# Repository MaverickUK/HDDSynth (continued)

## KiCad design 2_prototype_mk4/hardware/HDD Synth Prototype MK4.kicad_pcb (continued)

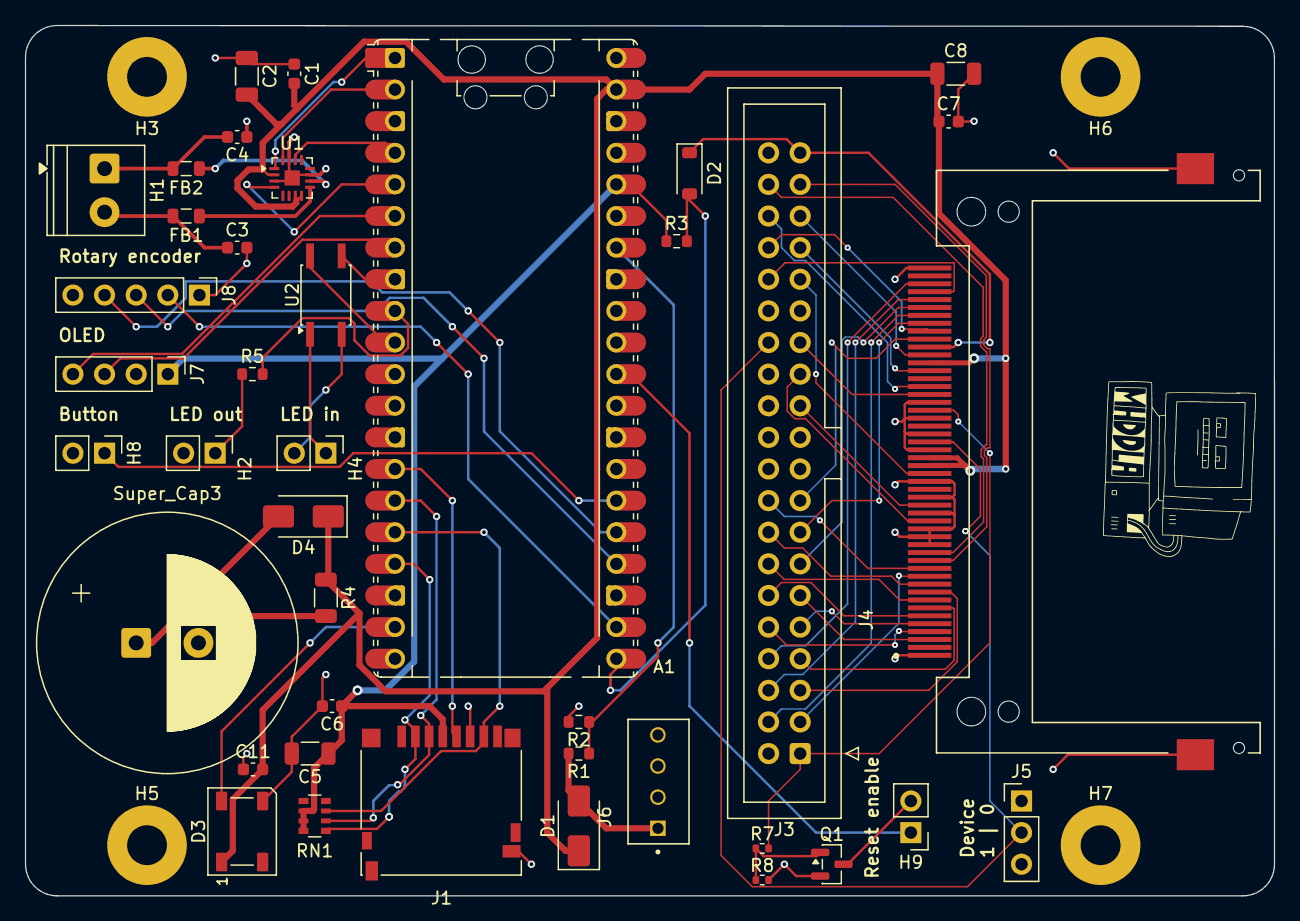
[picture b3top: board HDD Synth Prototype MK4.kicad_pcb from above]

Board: 2 copper layers, 100.3 x 69.9 mm, 44 parts (0 on the bottom side), 64 nets.

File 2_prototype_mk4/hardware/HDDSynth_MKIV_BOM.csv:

"Reference","Qty","Value","DNP","Exclude from BOM","Exclude from Board","Footprint","Datasheet","Description"
"A1","1","RaspberryPi_Pico2","","","","Module:RaspberryPi_Pico_Common_Unspecified","https://pip-assets.raspberrypi.com/categories/1005-raspberry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","High-performance microcontroller module featuring the RP2350 chip; dual-core ARM Cortex-M33 or Hazard3 RISC-V processors up to 150 MHz, 520kB SRAM, and 4MB off-chip QSPI flash"
"C1,C6,C7","3","0.1uF","","","","Capacitor_SMD:C_0603_1608Metric","","Unpolarized capacitor"
"C2,C5,C8","3","10uF","","","","Capacitor_SMD:C_1206_3216Metric","","Unpolarized capacitor"
"C3,C4","2","1nF","","","","Capacitor_SMD:C_0603_1608Metric","","Unpolarized capacitor, small symbol"
"C9,C10","2","100nF","","","","Capacitor_SMD:C_0402_1005Metric","","Unpolarized capacitor"
"D1","1","SS14","","","","Diode_SMD:D_SMA","","1A, 40V Schottky diode"
"D2","1","BAT43W","","","","Diode_SMD:D_SOD-123","","Schottky Barrier Diode, Low Forward Voltage (Vf ≈ 0.3V), 30V 200mA,"
"D4","1","SS12","","","","Diode_SMD:D_SMA","","Schottky diode"
"FB1,FB2","2","FerriteBead_Small","","","","Inductor_SMD:L_0805_2012Metric","","Ferrite bead, small symbol"
"H1","1","Conn_01x02","","","","TerminalBlock_Phoenix:TerminalBlock_Phoenix_PT-1,5-2-3.5-H_1x02_P3.50mm_Horizontal","","Generic connector, single row, 01x02, script generated (kicad-library-utils/schlib/autogen/connector/)"
"H2,H4,H8","3","Conn_01x02","","","","Connector_PinHeader_2.54mm:PinHeader_1x02_P2.54mm_Vertical","","Generic connector, single row, 01x02, script generated (kicad-library-utils/schlib/autogen/connector/)"
"J1","1","Micro_SD_Card","","","","Connector_Card:microSD_HC_Hirose_DM3D-SF","","Micro SD Card Socket - Hirose DM3D-SF"
"J3","1","Conn_02x20_Odd_Even","","","","Connector_IDC:IDC-Header_2x20_P2.54mm_Vertical","https://www.lcsc.com/product-detail/C19193815.html?s_z=n_q_p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","Generic connector, double row, 02x20, odd/even pin numbering scheme (row 1 odd numbers, row 2 even numbers), script generated (kicad-library-utils/schlib/autogen/connector/)"
"J4","1","1734451-1","","","","Custom:TE_1734451-1","https://www.snapeda.com/parts/1734451-1/TE%20Connectivity/vi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","50 Position Card Connector CompactFlash® - Type I, II Surface Mount, Right Angle Gold"
"J5","1","Conn_01x03_Pin","","","","Connector_PinHeader_2.54mm:PinHeader_1x03_P2.54mm_Vertical","","Generic connector, single row, 01x03, script generated"
"J6","1","171825-4","","","","Custom:TE_171825-4","","CONNECTOR, EIS, TYPE V, HEADER, 4 POSITION, 2.50 MM CENTERLINE | TE Connectivity 171825-4"
"J7","1","Conn_01x04_Pin","","","","Connector_PinHeader_2.54mm:PinHeader_1x04_P2.54mm_Vertical","","Generic connector, single row, 01x04, script generated"
"J8","1","Conn_01x05","","","","Connector_PinHeader_2.54mm:PinHeader_1x05_P2.54mm_Vertical","","Generic connector, single row, 01x05, script generated (kicad-library-utils/schlib/autogen/connector/)"
"R1","1","1K","","","","Resistor_SMD:R_0603_1608Metric","","Resistor"
"R2","1","2K","","","","Resistor_SMD:R_0603_1608Metric","","Resistor"
"R3","1","4.7K","","","","Resistor_SMD:R_0603_1608Metric","","Resistor"
"R4","1","33R","","","","Resistor_SMD:R_1206_3216Metric","","Resistor"
"R5","1","330R","","","","Resistor_SMD:R_0603_1608Metric","","Resistor"
"R6","1","10K","","","","Resistor_SMD:R_0402_1005Metric","","Resistor"
"RN1","1","47K","","","","Resistor_SMD:R_Array_Convex_4x0603","","4 resistor network, parallel topology"
"Super_Cap3","1","1F","","","","Capacitor_THT:CP_Radial_D14.0mm_P5.00mm","https://resources.kitronik.co.uk/pdf/super_capacitor.pdf","polarized radial super capacitor, 1F 5.5V"
"U1","1","MAX98357A","","","","Package_DFN_QFN:TQFN-16-1EP_3x3mm_P0.5mm_EP1.23x1.23mm","https://www.analog.com/media/en/technical-documentation/data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","Mono DAC with amplifier, I2S, PCM, TDM, 32-bit, 96khz, 3.2W, TQFP-16"
"U2","1","Optocoupler_DC_PhotoNPN_AKEC","","","","Package_SO:SO-4_4.4x3.6mm_P2.54mm","","Generic DC optocoupler with NPN phototransistor output, pins order: anode/cathode/emitter/collector"
"U3","1","TXS0101DBV","","","","Package_TO_SOT_SMD:SOT-23-6","https://www.ti.com/lit/ds/symlink/txs0101.pdf","1-Bit Bidirectional Voltage-Level Shifter for Open-Drain and Push-Pull Application, SOT-23"

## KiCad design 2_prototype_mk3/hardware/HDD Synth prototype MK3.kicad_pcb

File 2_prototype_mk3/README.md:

## HDD Synth
### Prototype MKIII

#### Hardware
Designed in KiCad and manufacufered by PCBWay with factory assembly of components

Uses mostly surface mounted components for ease of automated assembly and reduction in size and cost

#### Software
Runs CircuitPython for ease of development

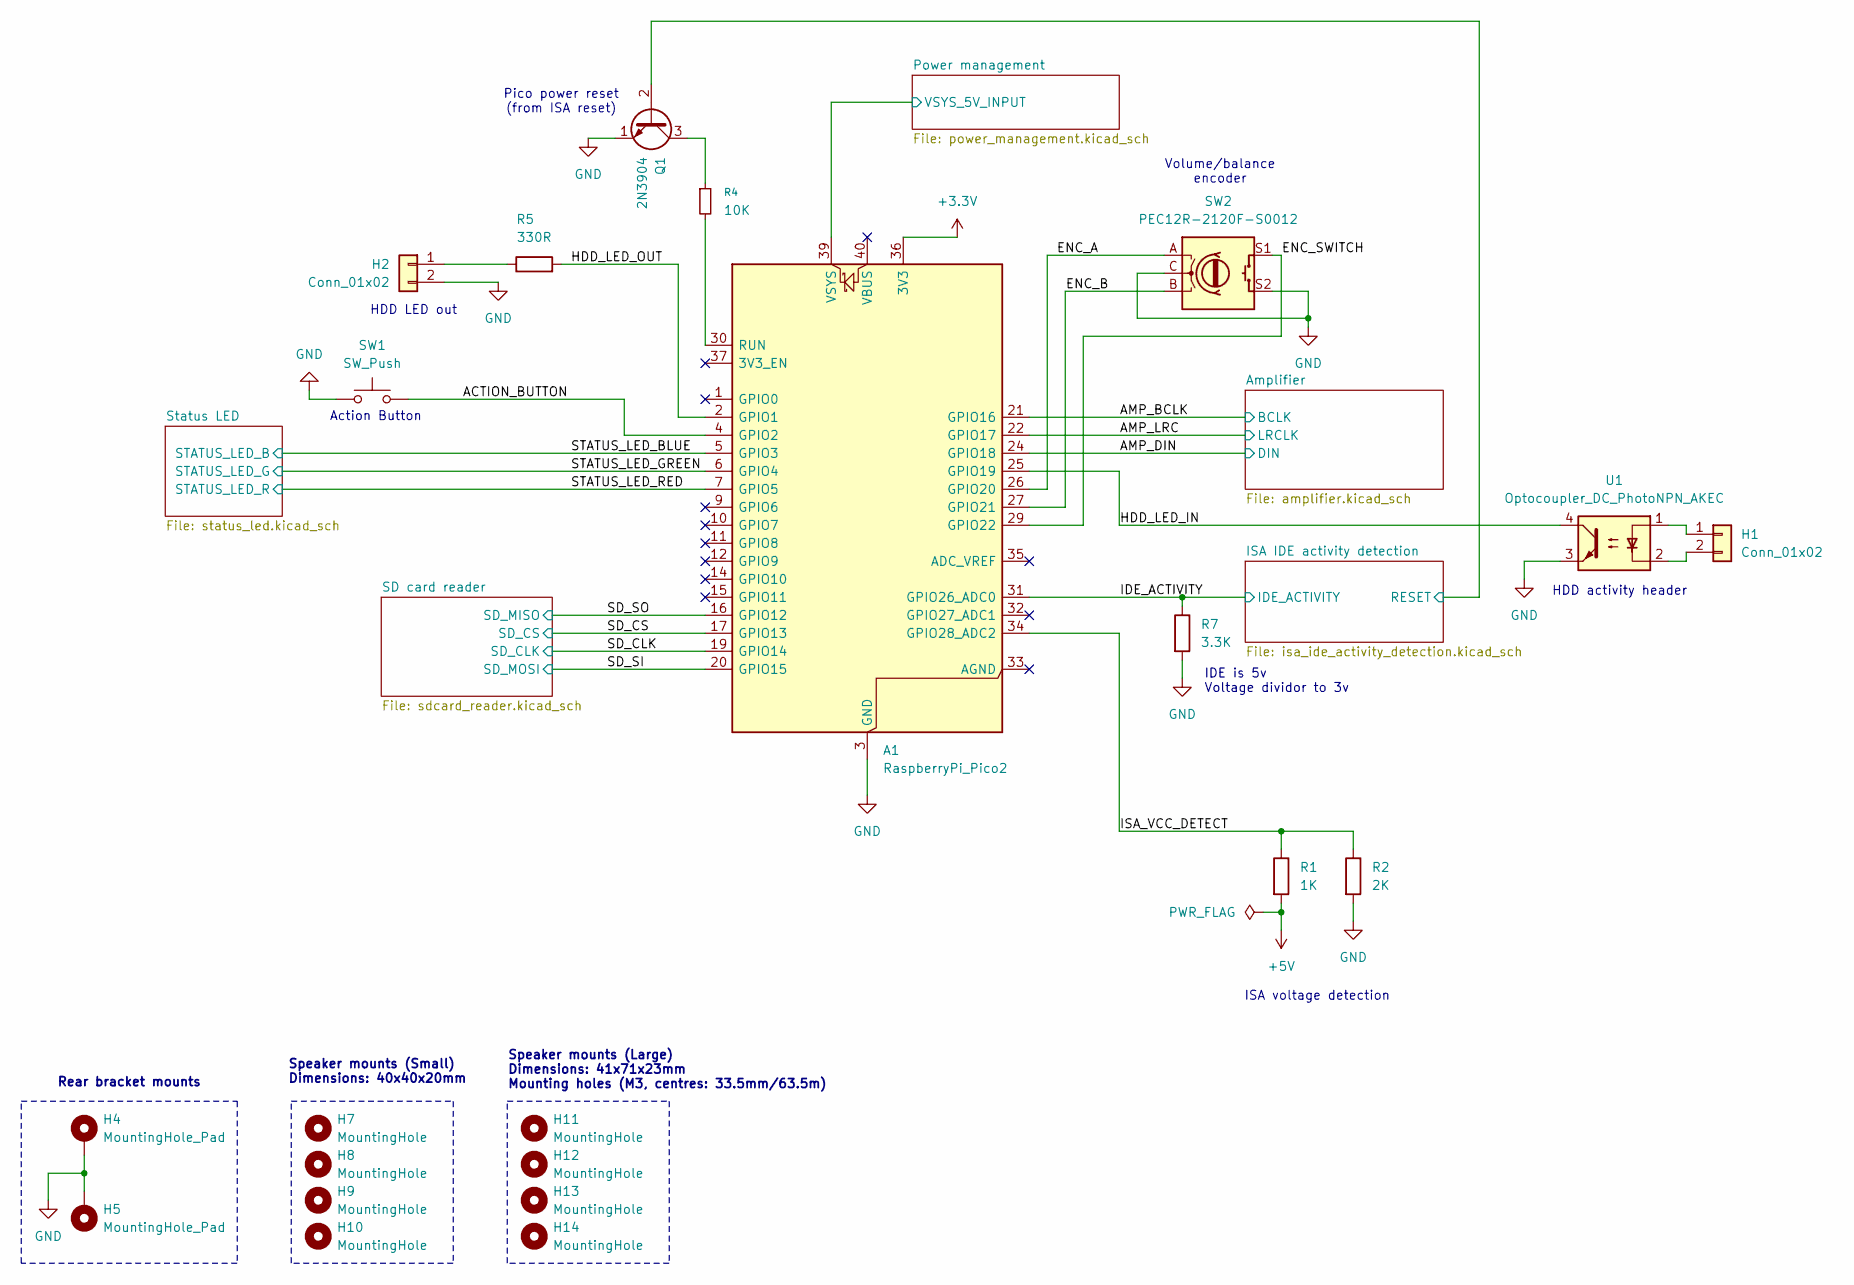
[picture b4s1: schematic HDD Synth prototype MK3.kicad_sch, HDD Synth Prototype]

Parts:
A1: RaspberryPi_Pico2; RaspberryPi_Pico_Common_Unspecified; Manufacturer_Part_Number SC1308; LCSC_Part_Number C41407547
H1, H2: Conn_01x02; PinHeader_1x02_P2.54mm_Vertical
H4, H5: MountingHole_Pad; MountingHole_3.2mm_M3_Pad_Via
H7, H8, H9, H10, H11, H12, H13, H14: MountingHole; MountingHole_3.2mm_M3
Q1: 2N3904; SOT-23; Manufacturer_Part_Number MMBT3904LT1G; LCSC_Part_Number C50176433
R1: 1K; R_0603_1608Metric; Manufacturer_Part_Number RC0603FR-071KL
R2: 2K; R_0603_1608Metric; Manufacturer_Part_Number RC0603FR-072KL
R4: 10K; R_0603_1608Metric; Manufacturer_Part_Number RC0603FR-0710KL
R5: 330R; R_0603_1608Metric; Manufacturer_Part_Number RC0603FR-07330RL
R7: 3.3K; R_0603_1608Metric; Manufacturer_Part_Number RC0603FR-073K3L
SW1: SW_Push; PTS645VL582LFS; Manufacturer_Part_Number PTS645VL582LFS; LCSC_Part_Number C285525
SW2: PEC12R-2120F-S0012; RotaryEncoder_Bourns_Horizontal_PEC12R-2x17F-Sxxxx; Manufacturer_Part_Number PEC12R-2120F-S0012; LCSC_Part_Number PEC12R-2220F-S0024
U1: Optocoupler_DC_PhotoNPN_AKEC; SO-4_4.4x3.6mm_P2.54mm; Manufacturer_Part_Number EL357N(C)(TA)-VG; LCSC_Part_Number C2916312

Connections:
+3.3V: A1.36 (3V3); also elsewhere on the board
+5V: R1.2; also elsewhere on the board
/ACTION_BUTTON: A1.4 (GPIO2), SW1.2
/AMP_BCLK: A1.21 (GPIO16); also elsewhere on the board
/AMP_DIN: A1.24 (GPIO18); also elsewhere on the board
/AMP_LRC: A1.22 (GPIO17); also elsewhere on the board
/ENC_A: A1.26 (GPIO20), SW2.A
/ENC_B: A1.27 (GPIO21), SW2.B
/ENC_SWITCH: A1.29 (GPIO22), SW2.S1
/HDD_LED_IN: A1.25 (GPIO19), U1.4
/HDD_LED_OUT: A1.2 (GPIO1), R5.2
/IDE_ACTIVITY: A1.31 (GPIO26_ADC0), R7.1; also elsewhere on the board
/ISA IDE activity detection/RESET: Q1.2 (B); also elsewhere on the board
/ISA_VCC_DETECT: A1.34 (GPIO28_ADC2), R1.1, R2.1
/SD_CLK: A1.19 (GPIO14); also elsewhere on the board
/SD_CS: A1.17 (GPIO13); also elsewhere on the board
/SD_SI: A1.20 (GPIO15); also elsewhere on the board
/SD_SO: A1.16 (GPIO12); also elsewhere on the board
/STATUS_LED_BLUE: A1.5 (GPIO3); also elsewhere on the board
/STATUS_LED_GREEN: A1.6 (GPIO4); also elsewhere on the board
/STATUS_LED_RED: A1.7 (GPIO5); also elsewhere on the board
GND: A1.3 (GND), A1.8 (GND), A1.13 (GND), A1.18 (GND), A1.23 (GND), A1.28 (GND), A1.38 (GND), H2.2, H4.1, H5.1, Q1.1 (E), R2.2, R7.2, SW1.1, SW2.C, SW2.S2, U1.3; also elsewhere on the board
unnamed: A1.30 (RUN), R4.2
unnamed: H1.1, U1.1
unnamed: H1.2, U1.2
unnamed: H2.1, R5.1
unnamed: Q1.3 (C), R4.1
POWER_5V_SUP: A1.39 (VSYS); also elsewhere on the board

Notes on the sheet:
HDD activity header
Volume/balance encoder
Pico power reset (from ISA reset)
Rear bracket mounts
Speaker mounts (Small) Dimensions: 40x40x20mm
ISA voltage detection
IDE is 5v Voltage dividor to 3v
Action Button
HDD LED out
Speaker mounts (Large) Dimensions: 41x71x23mm Mounting holes (M3, centres: 33.5mm/63.5m)

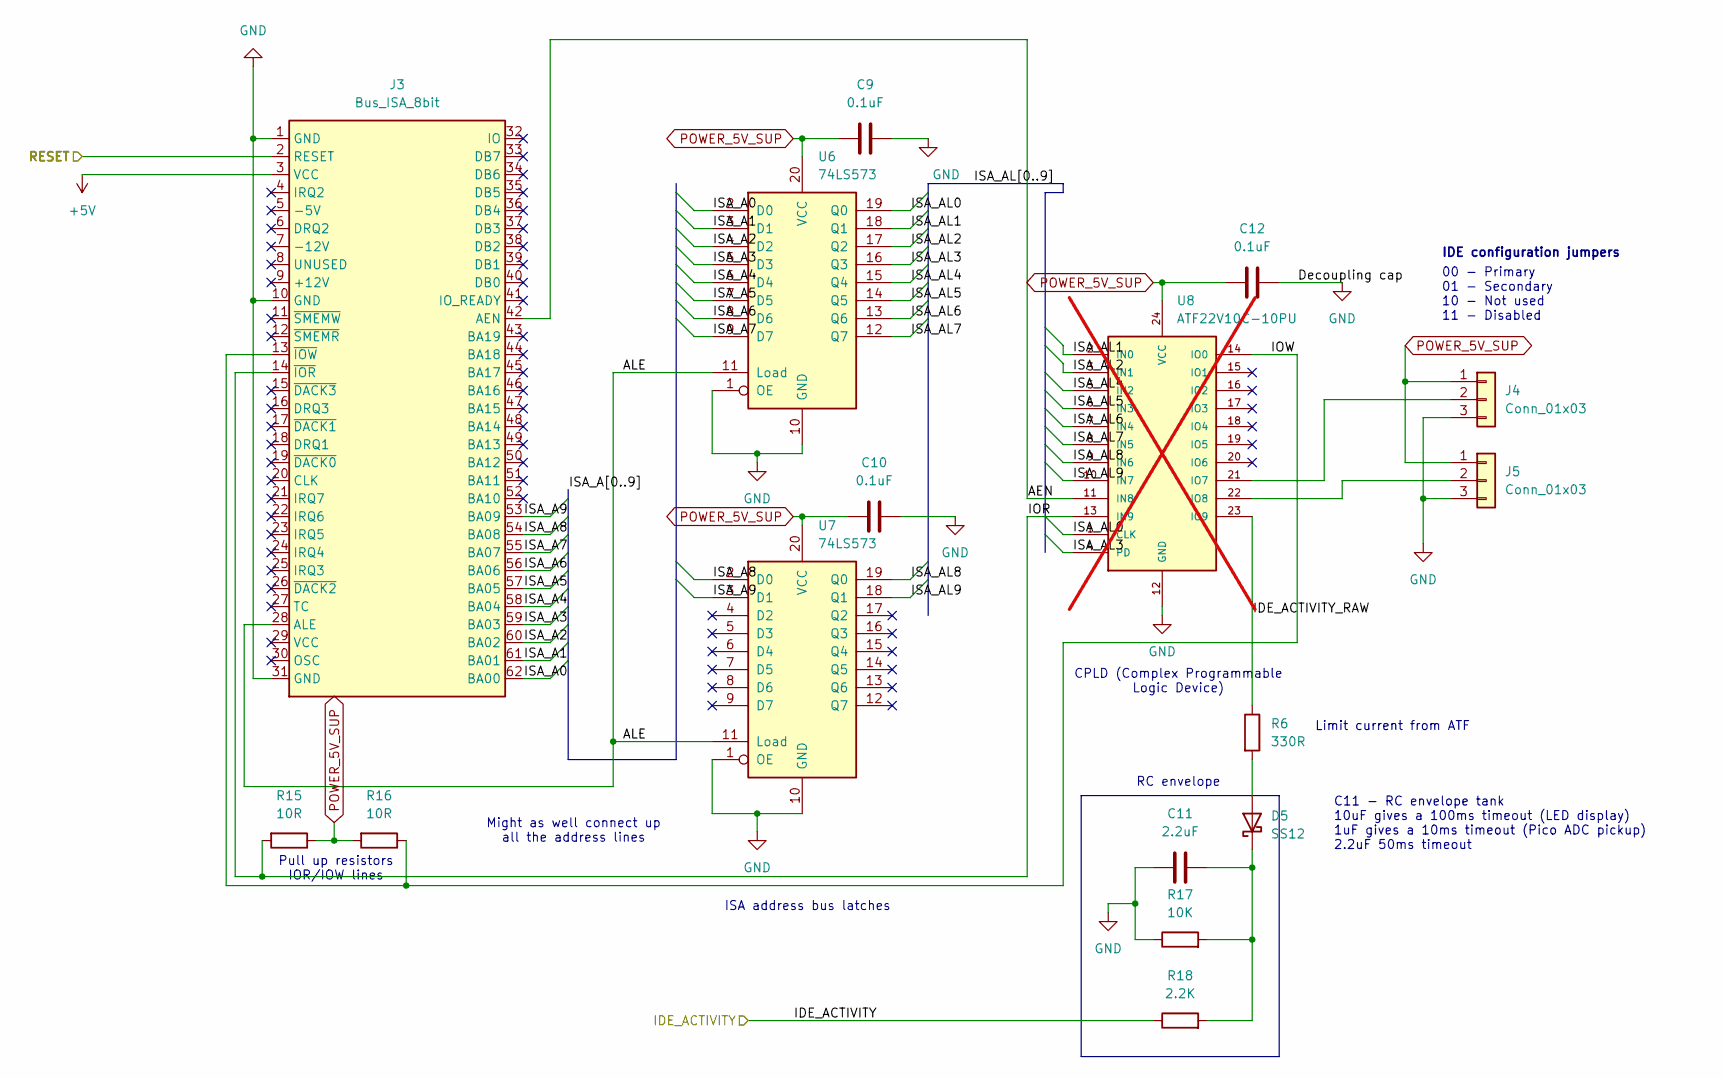
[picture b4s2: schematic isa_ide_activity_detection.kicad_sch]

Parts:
C9, C10, C12: 0.1uF; C_0603_1608Metric; Manufacturer_Part_Number CL10B104KO8NNNC
C11: 2.2uF; C_1206_3216Metric; Manufacturer_Part_Number CL31B225KCHNNNE
D5: SS12; D_SMA; Manufacturer_Part_Number SS12
J3: Bus_ISA_8bit; BUS_AT_8bit
J4, J5: Conn_01x03; PinHeader_1x03_P2.54mm_Vertical
R6: 330R; R_0603_1608Metric; Manufacturer_Part_Number RC0603FR-07330RL
R15, R16: 10R; R_0603_1608Metric; Manufacturer_Part_Number RC0603FR-0710RL
R17: 10K; R_0603_1608Metric; Manufacturer_Part_Number RC0603FR-0710KL
R18: 2.2K; R_0603_1608Metric; Manufacturer_Part_Number RC0603FR-072K2L
U6, U7: 74LS573; TSSOP-20_4.4x6.5mm_P0.65mm; Manufacturer_Part_Number SN74HC573APWR
U8: ATF22V10C-10PU; DIP-24_W7.62mm_Socket; not fitted

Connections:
+5V: J3.3 (VCC); also elsewhere on the board
/IDE_ACTIVITY: R18.1; also elsewhere on the board
/ISA IDE activity detection/AEN: J3.42 (AEN), U8.11 (IN8)
/ISA IDE activity detection/ALE: J3.28 (ALE), U6.11 (Load), U7.11 (Load)
/ISA IDE activity detection/IDE_ACTIVITY_RAW: R6.1, U8.23 (IO9)
/ISA IDE activity detection/IOR: J3.14 (~IOR), R15.2, U8.13 (IN9)
/ISA IDE activity detection/IOW: J3.13 (~IOW), R16.1, U8.14 (IO0)
/ISA IDE activity detection/ISA_A0: J3.62 (BA00), U6.2 (D0)
/ISA IDE activity detection/ISA_A1: J3.61 (BA01), U6.3 (D1)
/ISA IDE activity detection/ISA_A2: J3.60 (BA02), U6.4 (D2)
/ISA IDE activity detection/ISA_A3: J3.59 (BA03), U6.5 (D3)
/ISA IDE activity detection/ISA_A4: J3.58 (BA04), U6.6 (D4)
/ISA IDE activity detection/ISA_A5: J3.57 (BA05), U6.7 (D5)
/ISA IDE activity detection/ISA_A6: J3.56 (BA06), U6.8 (D6)
/ISA IDE activity detection/ISA_A7: J3.55 (BA07), U6.9 (D7)
/ISA IDE activity detection/ISA_A8: J3.54 (BA08), U7.2 (D0)
/ISA IDE activity detection/ISA_A9: J3.53 (BA09), U7.3 (D1)
/ISA IDE activity detection/ISA_AL0: U6.19 (Q0), U8.1 (CLK)
/ISA IDE activity detection/ISA_AL1: U6.18 (Q1), U8.2 (IN0)
/ISA IDE activity detection/ISA_AL2: U6.17 (Q2), U8.3 (IN1)
/ISA IDE activity detection/ISA_AL3: U6.16 (Q3), U8.4 (PD)
/ISA IDE activity detection/ISA_AL4: U6.15 (Q4), U8.5 (IN2)
/ISA IDE activity detection/ISA_AL5: U6.14 (Q5), U8.6 (IN3)
/ISA IDE activity detection/ISA_AL6: U6.13 (Q6), U8.7 (IN4)
/ISA IDE activity detection/ISA_AL7: U6.12 (Q7), U8.8 (IN5)
/ISA IDE activity detection/ISA_AL8: U7.19 (Q0), U8.9 (IN6)
/ISA IDE activity detection/ISA_AL9: U7.18 (Q1), U8.10 (IN7)
/ISA IDE activity detection/RESET: J3.2 (RESET); also elsewhere on the board
GND: C9.2, C10.2, C11.1, C12.2, J3.1 (GND), J3.10 (GND), J3.31 (GND), J4.3, J5.3, R17.1, U6.1 (OE), U6.10 (GND), U7.1 (OE), U7.10 (GND), U8.12 (GND); also elsewhere on the board
unnamed: D5.2 (A), R6.2
unnamed: C11.2, D5.1 (K), R17.2, R18.2
unnamed: J4.2, U8.21 (IO7)
unnamed: J5.2, U8.22 (IO8)
POWER_5V_SUP: C9.1, C10.1, C12.1, J4.1, J5.1, R15.1, R16.2, U6.20 (VCC), U7.20 (VCC), U8.24 (VCC); also elsewhere on the board

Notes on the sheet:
Might as well connect up all the address lines
Pull up resistors IOR/IOW lines
Limit current from ATF
CPLD (Complex Programmable Logic Device)
00 - Primary 01 - Secondary 10 - Not used 11 - Disabled
C11 - RC envelope tank 10uF gives a 100ms timeout (LED display) 1uF gives a 10ms timeout (Pico ADC pickup) 2.2uF 50ms timeout
IDE configuration jumpers
ISA address bus latches
RC envelope

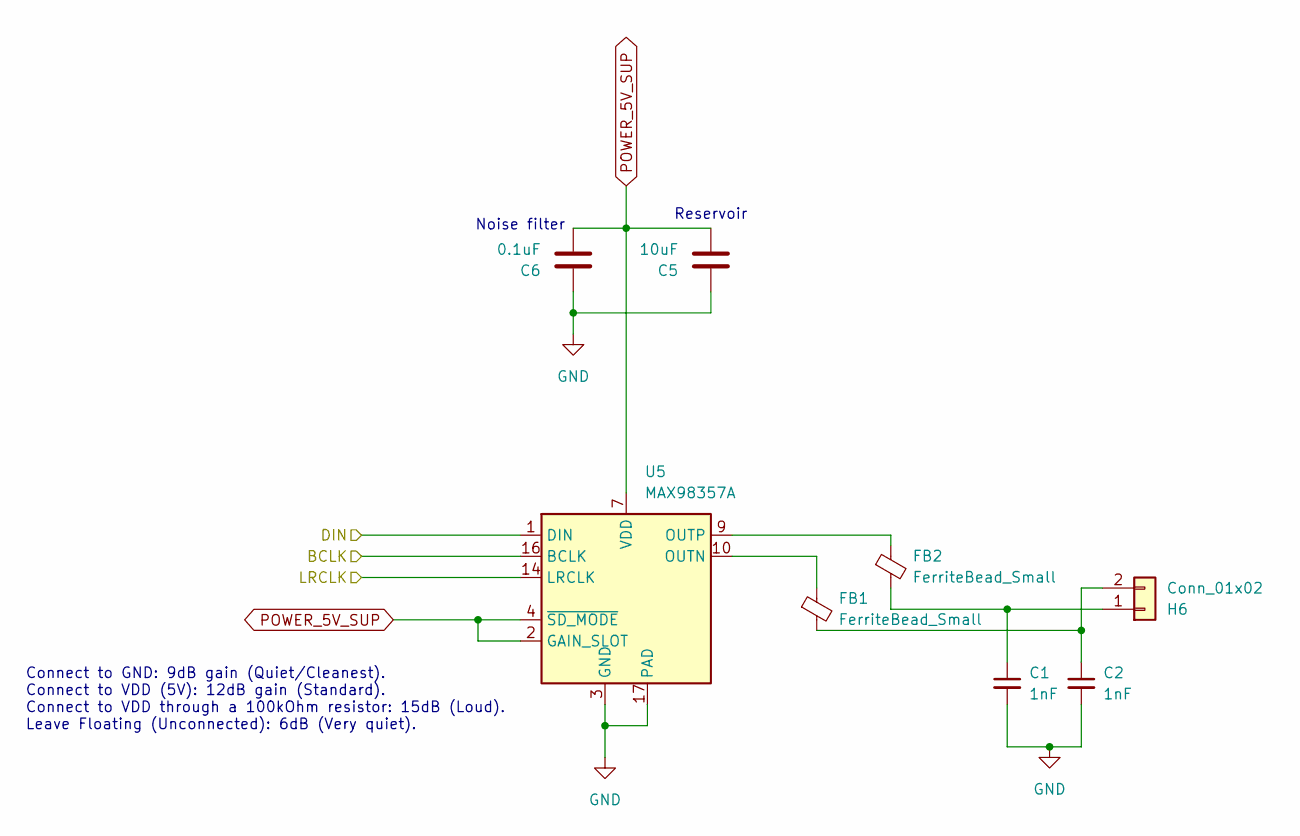
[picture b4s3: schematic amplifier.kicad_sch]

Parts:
C1, C2: 1nF; C_0603_1608Metric; Manufacturer_Part_Number 0603B102K500NT
C5: 10uF; C_1206_3216Metric; Manufacturer_Part_Number CL31A106KAHNNNE
C6: 0.1uF; C_0603_1608Metric; Manufacturer_Part_Number CL10B104KO8NNNC
FB1, FB2: FerriteBead_Small; L_0805_2012Metric; Manufacturer_Part_Number BLM21PG221SN1D; LCSC_Part_Number C85840
H6: Conn_01x02; TerminalBlock_Phoenix_PT-1,5-2-3.5-H_1x02_P3.50mm_Horizontal; Manufacturer_Part_Number 1984617; LCSC_Part_Number C3819527
U5: MAX98357A; TQFN-16-1EP_3x3mm_P0.5mm_EP1.23x1.23mm; Manufacturer_Part_Number MAX98357AETE+T; LCSC_Part_Number C910544

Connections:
/AMP_BCLK: U5.16 (BCLK); also elsewhere on the board
/AMP_DIN: U5.1 (DIN); also elsewhere on the board
/AMP_LRC: U5.14 (LRCLK); also elsewhere on the board
GND: C1.2, C2.2, C5.1, C6.1, U5.3 (GND), U5.11 (GND), U5.15 (GND), U5.17 (PAD); also elsewhere on the board
unnamed: C1.1, FB2.2, H6.1
unnamed: C2.1, FB1.2, H6.2
unnamed: FB1.1, U5.10 (OUTN)
unnamed: FB2.1, U5.9 (OUTP)
POWER_5V_SUP: C5.2, C6.2, U5.2 (GAIN_SLOT), U5.4 (~SD_MODE), U5.7 (VDD), U5.8 (VDD); also elsewhere on the board

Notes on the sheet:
Connect to GND: 9dB gain (Quiet/Cleanest). Connect to VDD (5V): 12dB gain (Standard). Connect to VDD through a 100kOhm resistor: 15dB (Loud). Leave Floating (Unconnected): 6dB (Very quiet).
Reservoir
Noise filter

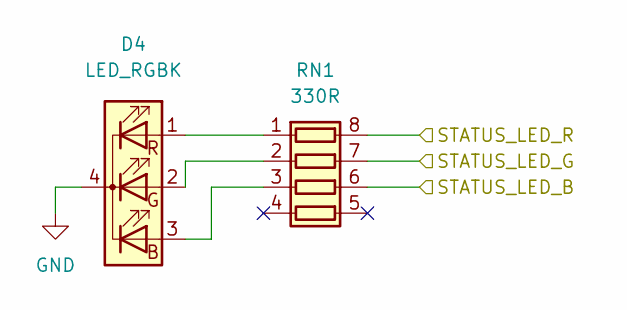
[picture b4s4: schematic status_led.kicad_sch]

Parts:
D4: LED_RGBK; LED_D5.0mm-4_RGB; Manufacturer_Part_Number LF05RGB-01; LCSC_Part_Number C330759
RN1: 330R; R_Array_Convex_4x0603; Manufacturer_Part_Number YC164-JR-07330RL; LCSC_Part_Number C136828

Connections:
/STATUS_LED_BLUE: RN1.6 (R3.2); also elsewhere on the board
/STATUS_LED_GREEN: RN1.7 (R2.2); also elsewhere on the board
/STATUS_LED_RED: RN1.8 (R1.2); also elsewhere on the board
GND: D4.4 (K); also elsewhere on the board
unnamed: D4.3 (BA), RN1.3 (R3.1)
unnamed: D4.2 (GA), RN1.2 (R2.1)
unnamed: D4.1 (RA), RN1.1 (R1.1)

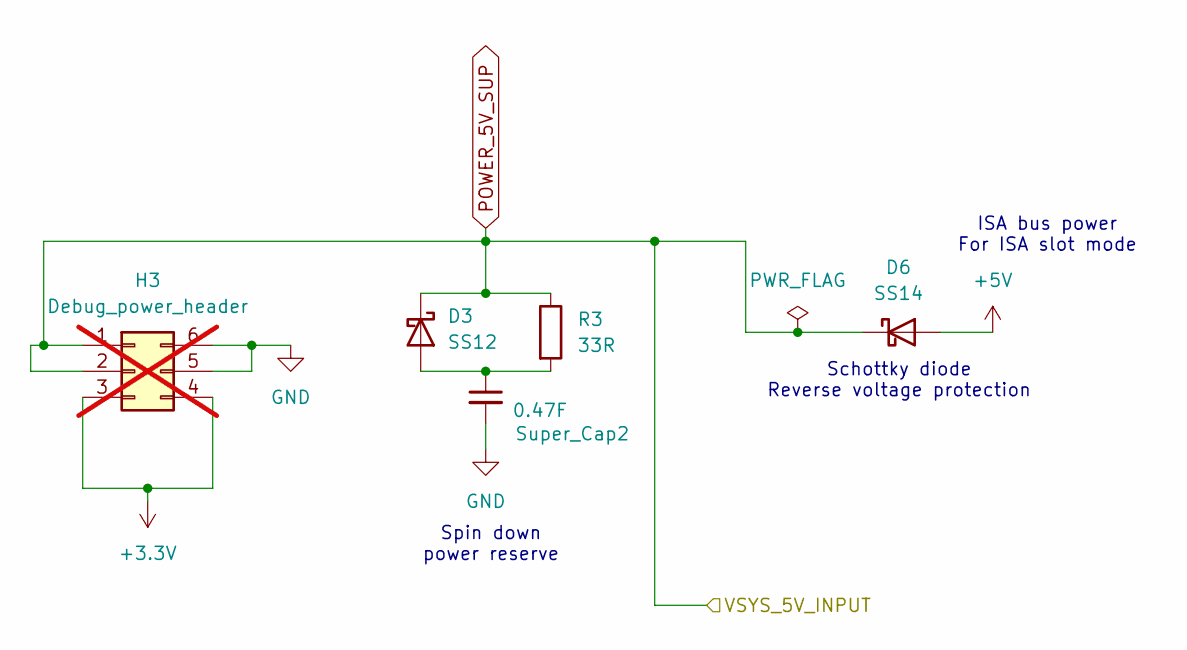
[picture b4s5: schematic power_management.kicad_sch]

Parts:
D3: SS12; D_SMA; Manufacturer_Part_Number SS12; LCSC_Part_Number C184027
D6: SS14; D_SMA; Manufacturer_Part_Number SS14; LCSC_Part_Number C83852
H3: Debug_power_header; PinHeader_2x03_P2.54mm_Vertical; not fitted
R3: 33R; R_1206_3216Metric; Manufacturer_Part_Number RC1206FR-0733RL
Super_Cap2: 0.47F; CP_Radial_D12.5mm_P5.00mm; Manufacturer_Part_Number DX-5R5V474U

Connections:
+3.3V: H3.3, H3.4; also elsewhere on the board
+5V: D6.2 (A); also elsewhere on the board
GND: H3.5, H3.6, Super_Cap2.2; also elsewhere on the board
unnamed: D3.2 (A), R3.2, Super_Cap2.1
POWER_5V_SUP: D3.1 (K), D6.1 (K), H3.1, H3.2, R3.1; also elsewhere on the board

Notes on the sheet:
ISA bus power For ISA slot mode
Spin down power reserve
Schottky diode Reverse voltage protection

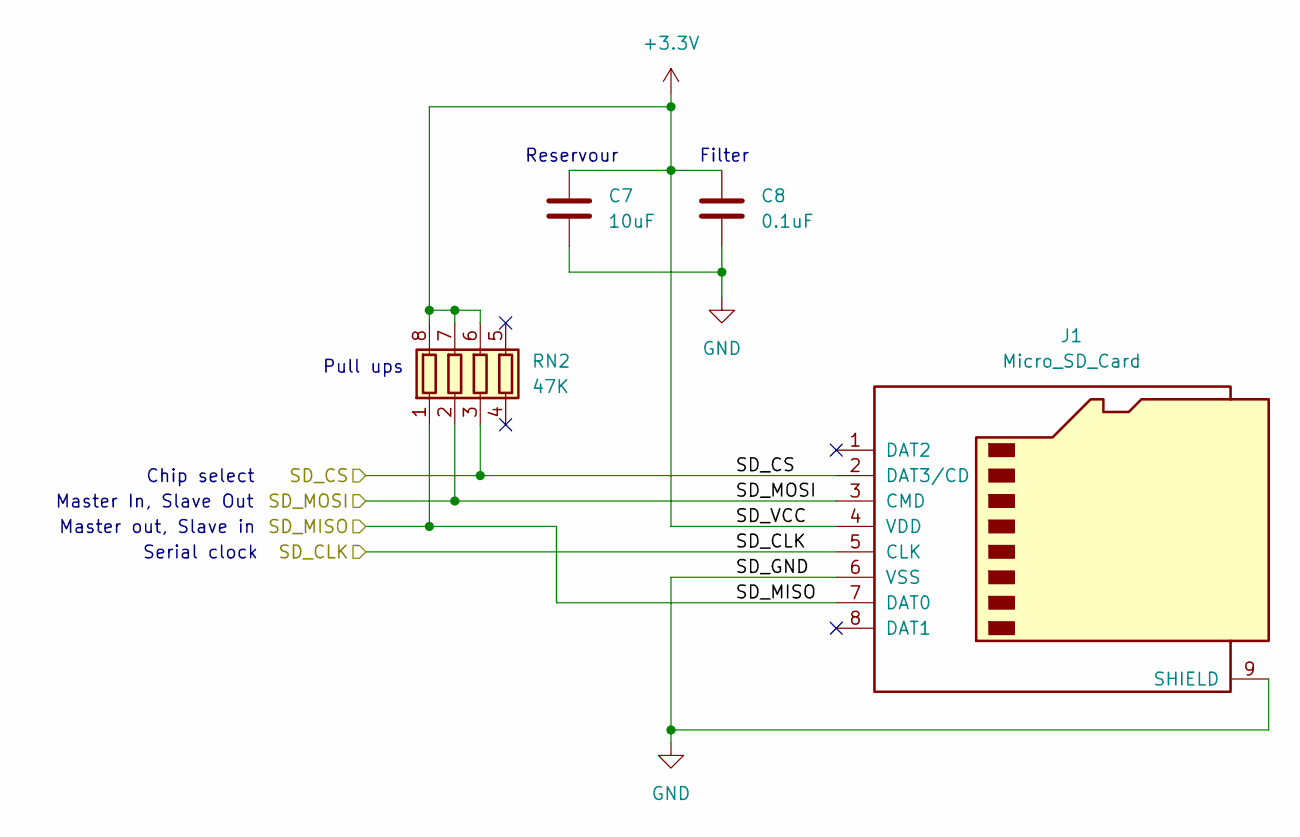
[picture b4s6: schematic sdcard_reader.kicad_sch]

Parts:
C7: 10uF; C_1206_3216Metric; Manufacturer_Part_Number CL31A106KAHNNNE
C8: 0.1uF; C_0603_1608Metric; Manufacturer_Part_Number CL10B104KO8NNNC
J1: Micro_SD_Card; microSD_HC_Hirose_DM3AT-SF-PEJM5; Manufacturer_Part_Number DM3D-SF; LCSC_Part_Number C719027
RN2: 47K; R_Array_Convex_4x0603; Manufacturer_Part_Number YC164-JR-0747KL; LCSC_Part_Number C779384

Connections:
+3.3V: C7.1, C8.1, J1.4 (VDD), RN2.6 (R3.2), RN2.7 (R2.2), RN2.8 (R1.2); also elsewhere on the board
/SD_CLK: J1.5 (CLK); also elsewhere on the board
/SD_CS: J1.2 (DAT3/CD), RN2.3 (R3.1); also elsewhere on the board
/SD_SI: J1.3 (CMD), RN2.2 (R2.1); also elsewhere on the board
/SD_SO: J1.7 (DAT0), RN2.1 (R1.1); also elsewhere on the board
GND: C7.2, C8.2, J1.6 (VSS), J1.9 (SHIELD); also elsewhere on the board

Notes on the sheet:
Master In, Slave Out
Pull ups
Filter
Chip select
Master out, Slave in
Reservour
Serial clock

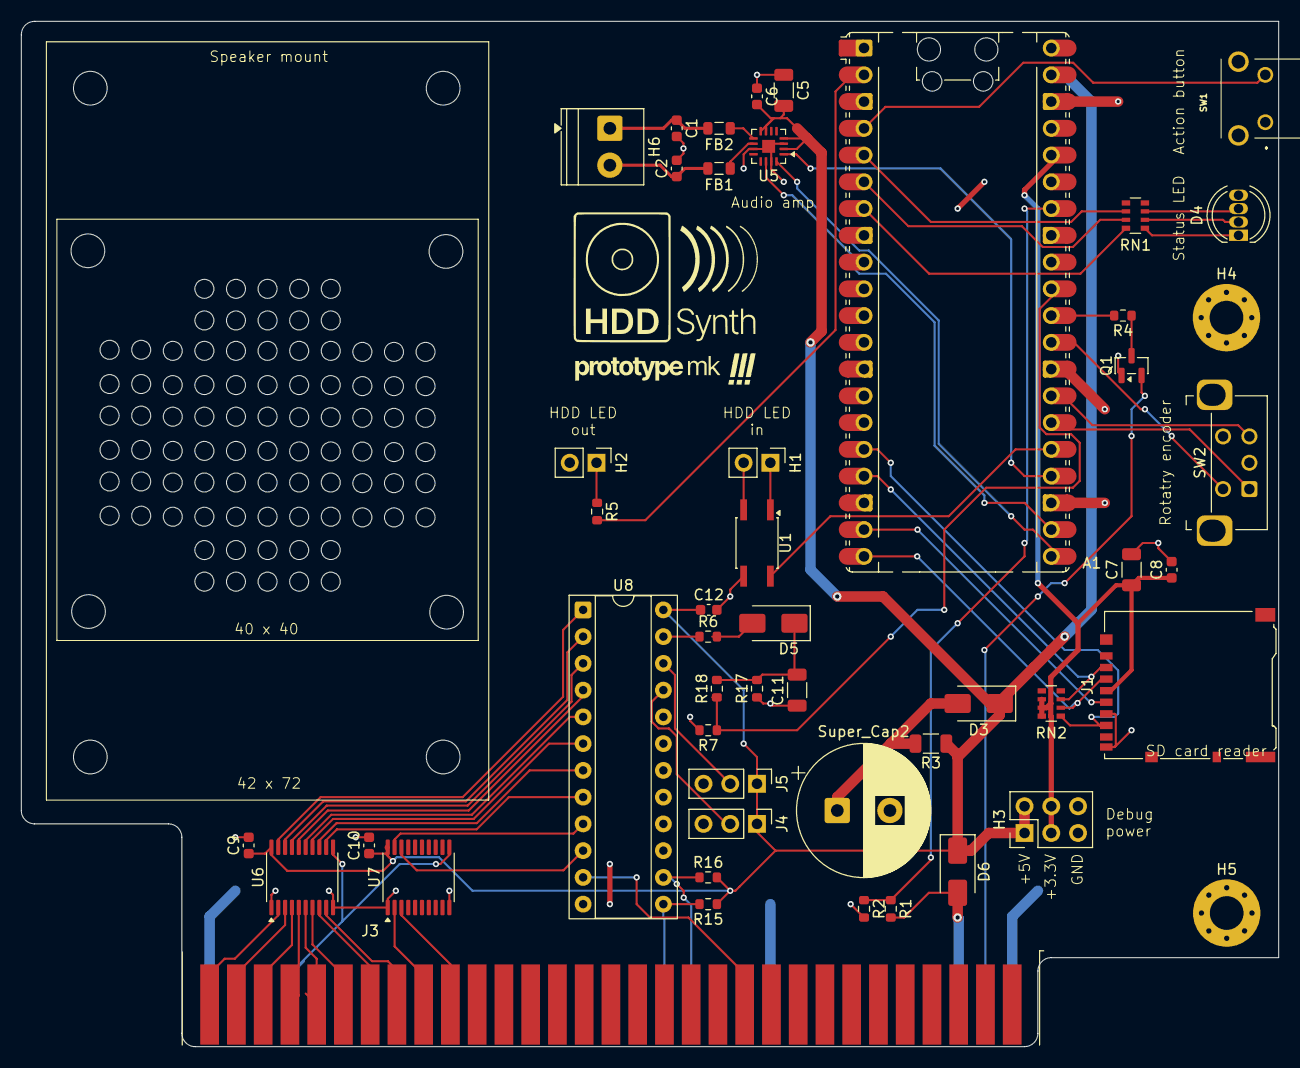
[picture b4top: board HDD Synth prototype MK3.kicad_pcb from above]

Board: 2 copper layers, 119.4 x 97.4 mm, 58 parts (1 on the bottom side), 65 nets.

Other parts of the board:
 : LOGO; MHDDLA_Sound_40mm

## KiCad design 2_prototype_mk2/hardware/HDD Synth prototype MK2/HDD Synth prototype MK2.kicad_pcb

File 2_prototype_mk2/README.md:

## HDD Synth
### Prototype MKII

#### Hardware
Designed in KiCad and manufacufered by PCBWay

Uses through hole components and breakout boards for the SD card reader and audio amp

#### Software
Runs CircuitPython for ease of development

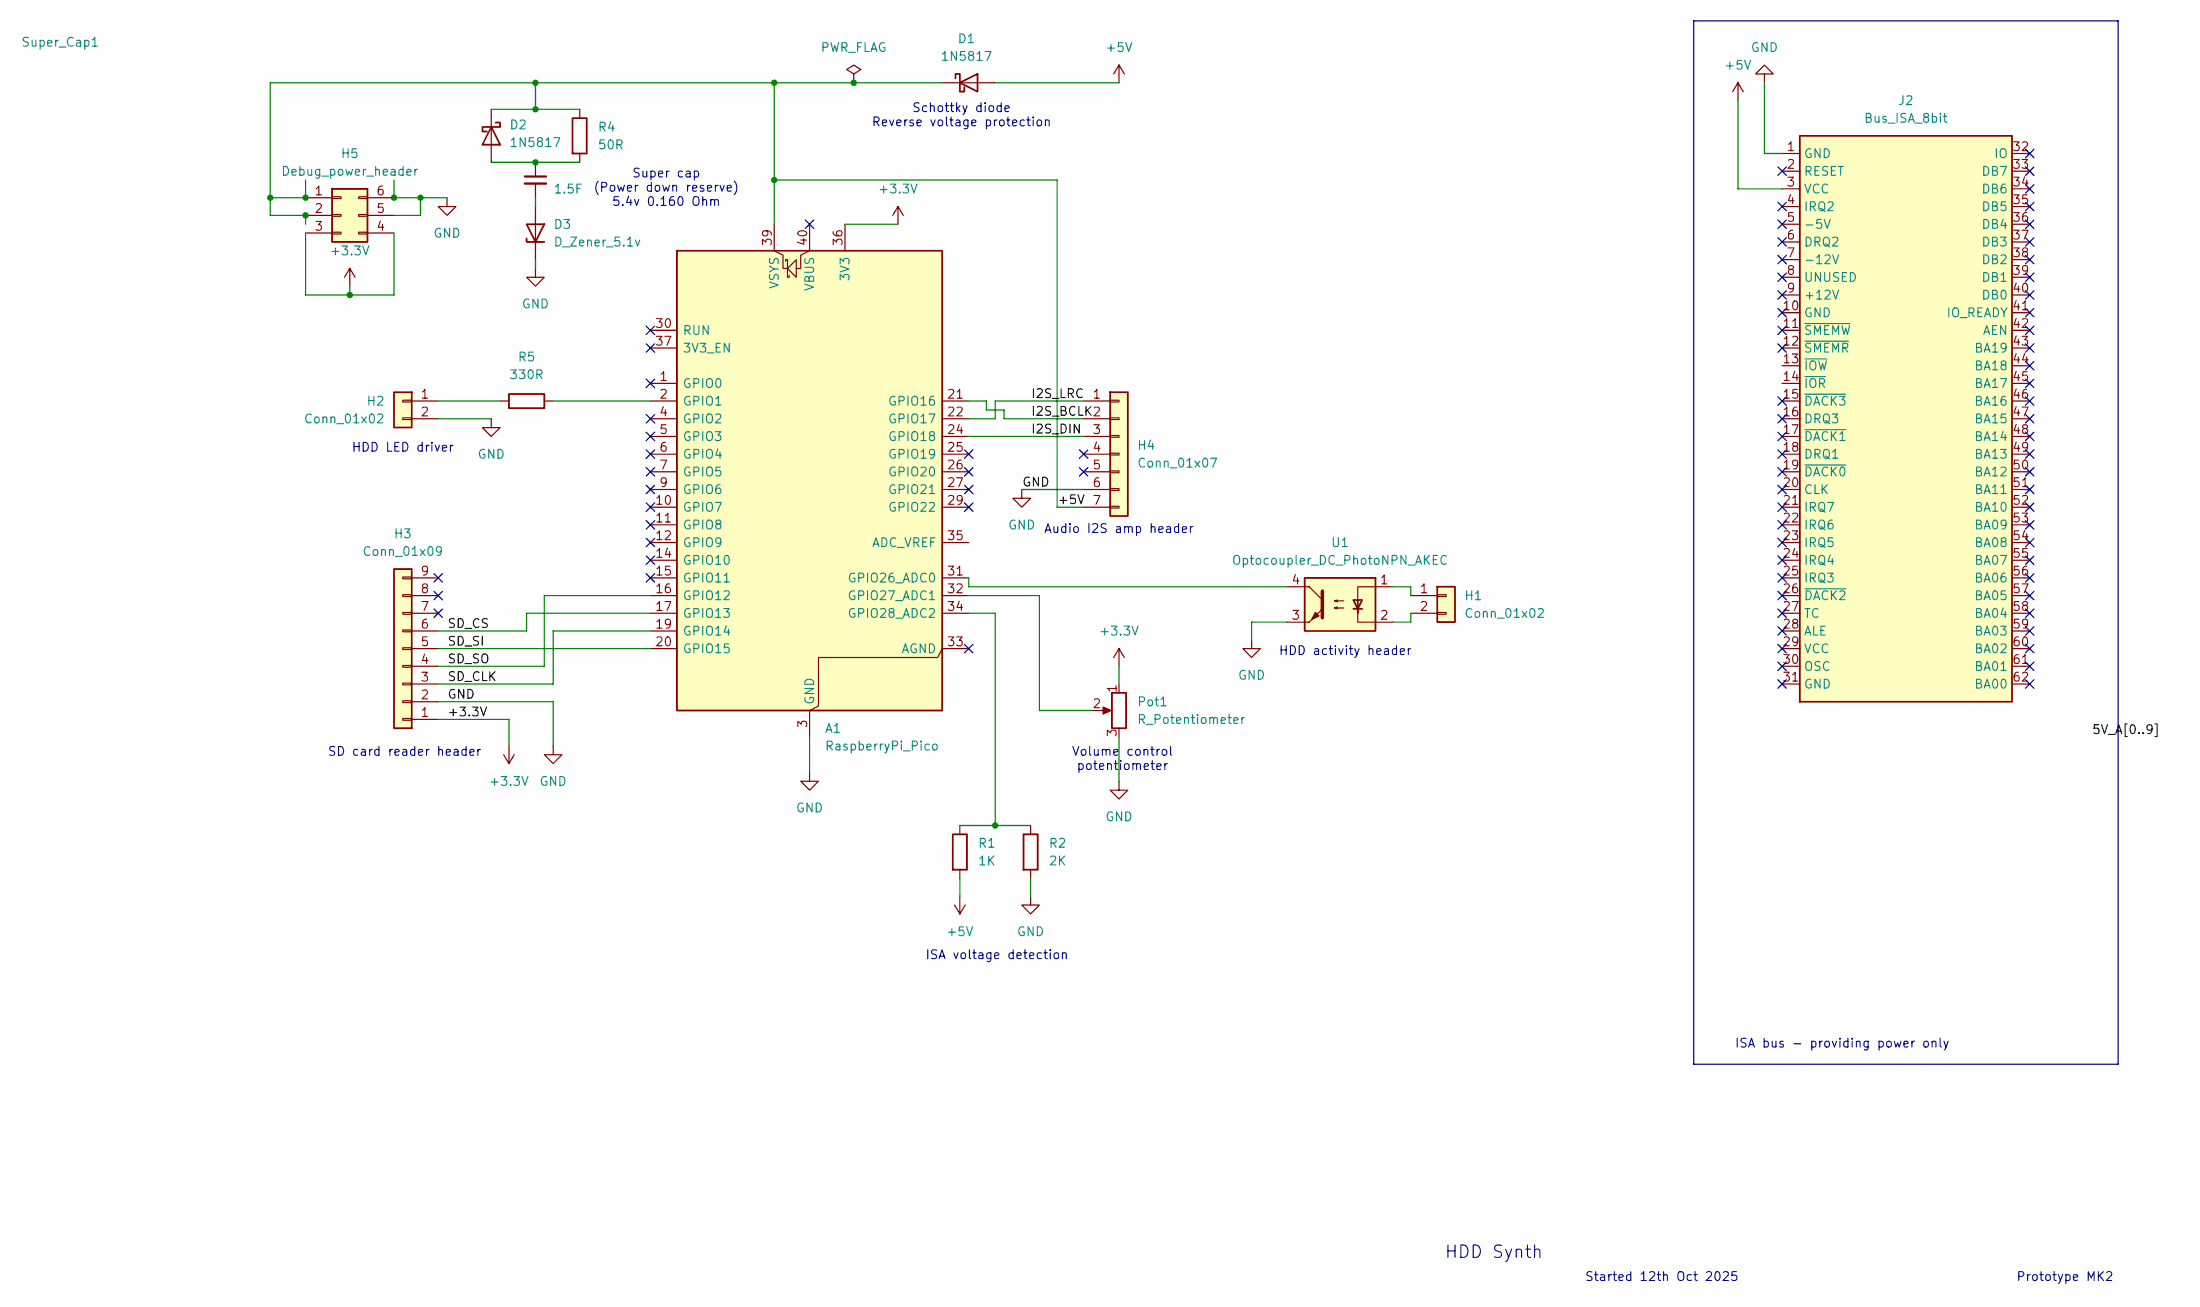
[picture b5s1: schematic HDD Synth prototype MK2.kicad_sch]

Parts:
A1: RaspberryPi_Pico; RaspberryPi_Pico_Common_Unspecified
D1, D2: 1N5817; D_DO-41_SOD81_P2.54mm_Vertical_AnodeUp
D3: D_Zener_5.1v; D_DO-35_SOD27_P7.62mm_Horizontal
H1, H2: Conn_01x02; PinHeader_1x02_P2.54mm_Vertical
H3: Conn_01x09; PinHeader_1x09_P2.54mm_Vertical
H4: Conn_01x07; PinHeader_1x07_P2.54mm_Vertical
H5: Debug_power_header; PinHeader_2x03_P2.54mm_Vertical
J2: Bus_ISA_8bit; BUS_AT
Pot1: R_Potentiometer; Potentiometer_Bourns_3386W_Horizontal
R1: 1K; R_Axial_DIN0207_L6.3mm_D2.5mm_P7.62mm_Horizontal
R2: 2K; R_Axial_DIN0207_L6.3mm_D2.5mm_P7.62mm_Horizontal
R4: 50R; R_Axial_DIN0207_L6.3mm_D2.5mm_P7.62mm_Horizontal
R5: 330R; R_Axial_DIN0207_L6.3mm_D2.5mm_P7.62mm_Horizontal
Super_Cap1: 1.5F; CP_Radial_D16.0mm_P7.50mm
U1: Optocoupler_DC_PhotoNPN_AKEC; DIP-4_W7.62mm

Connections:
+3.3V: A1.36 (3V3), H3.1, H5.3, H5.4, Pot1.1
+5V: A1.39 (VSYS), D1.1 (K), D1.2 (A), D2.1 (K), H4.7, H5.1, H5.2, J2.3 (VCC), R1.2, R4.1
/I2S_BCLK: A1.21 (GPIO16), H4.2
/I2S_DIN: A1.24 (GPIO18), H4.3
/I2S_LRC: A1.22 (GPIO17), H4.1
/SD_CLK: A1.19 (GPIO14), H3.3
/SD_CS: A1.17 (GPIO13), H3.6
/SD_SI: A1.20 (GPIO15), H3.5
/SD_SO: A1.16 (GPIO12), H3.4
GND: A1.3 (GND), A1.8 (GND), A1.13 (GND), A1.18 (GND), A1.23 (GND), A1.28 (GND), A1.38 (GND), D3.1 (K), H2.2, H3.2, H4.6, H5.5, H5.6, J2.1 (GND), Pot1.3, R2.2, U1.3
unnamed: A1.2 (GPIO1), R5.2
unnamed: A1.31 (GPIO26_ADC0), U1.4
unnamed: A1.32 (GPIO27_ADC1), Pot1.2
unnamed: A1.34 (GPIO28_ADC2), R1.1, R2.1
unnamed: D2.2 (A), R4.2, Super_Cap1.1
unnamed: D3.2 (A), Super_Cap1.2
unnamed: H1.1, U1.1
unnamed: H1.2, U1.2
unnamed: H2.1, R5.1

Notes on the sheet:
Super cap (Power down reserve) 5.4v 0.160 Ohm
HDD Synth
HDD activity header
Started 12th Oct 2025
Volume control potentiometer
ISA voltage detection
Prototype MK2
HDD LED driver
SD card reader header
ISA bus - providing power only
Schottky diode Reverse voltage protection
Audio I2S amp header
